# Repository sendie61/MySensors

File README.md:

# MySensors #
MySensors project. Wireless domotics sensors.<br>
Based on the open source project MySensors (http://www.mysensors.org)

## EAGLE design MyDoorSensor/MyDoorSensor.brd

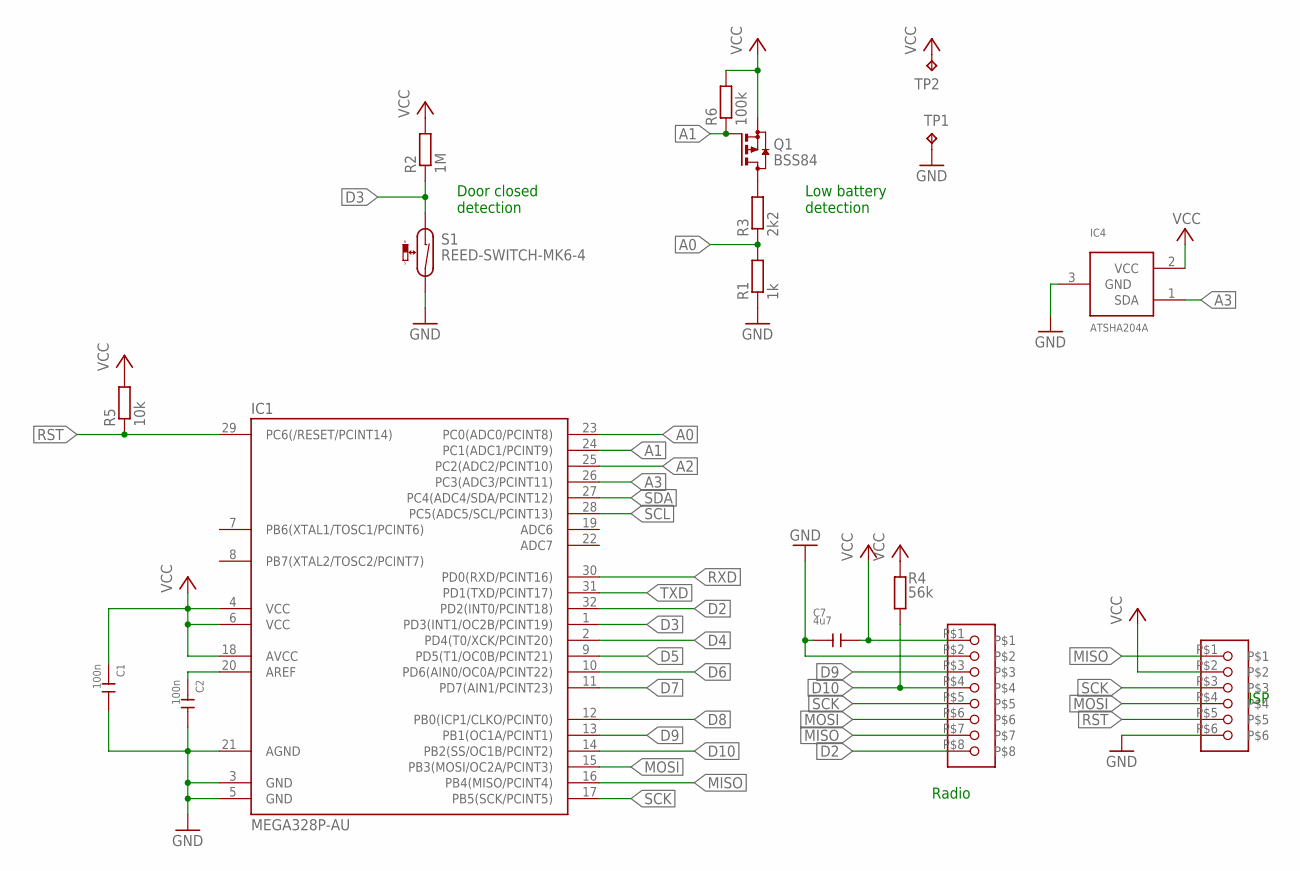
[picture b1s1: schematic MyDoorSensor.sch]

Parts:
C1, C2: 100n; C0603
C7: 4u7; C0805
IC1: MEGA328P-AU; TQFP32-08
IC4: ATSHA204A; SOT23
Q1: BSS84; SOT23
R1: 1k; R0805
R2: 1M; R0805
R3: 2k2; R0805
R4: 56k; R0805
R5: 10k; R0805
R6: 100k; R0805
S1: REED-SWITCH-MK6-4; MK6-4
TP1, TP2: TPPAD1-13; P1-13
U$1: NRF24; PINHD-1X08/NRF24
U$2: ISP

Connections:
A0: IC1.23 (PC0(ADC0/PCINT8)), R1.2, R3.1
A1: IC1.24 (PC1(ADC1/PCINT9)), Q1.1 (G), R6.1
A2: IC1.25 (PC2(ADC2/PCINT10))
A3: IC1.26 (PC3(ADC3/PCINT11)), IC4.1 (SDA)
D2: IC1.32 (PD2(INT0/PCINT18)), U$1.P$8
D3: IC1.1 (PD3(INT1/OC2B/PCINT19)), R2.1, S1.1
D4: IC1.2 (PD4(T0/XCK/PCINT20))
D5: IC1.9 (PD5(T1/OC0B/PCINT21))
D6: IC1.10 (PD6(AIN0/OC0A/PCINT22))
D7: IC1.11 (PD7(AIN1/PCINT23))
D8: IC1.12 (PB0(ICP1/CLKO/PCINT0))
D9: IC1.13 (PB1(OC1A/PCINT1)), U$1.P$3
D10: IC1.14 (PB2(SS/OC1B/PCINT2)), R4.1, U$1.P$4
GND: C1.2, C2.2, C7.1, IC1.3 (GND), IC1.5 (GND), IC1.21 (AGND), IC4.3 (GND), R1.1, S1.2, TP1.TP, U$1.P$2, U$2.P$6
MISO: IC1.16 (PB4(MISO/PCINT4)), U$1.P$7, U$2.P$1
MOSI: IC1.15 (PB3(MOSI/OC2A/PCINT3)), U$1.P$6, U$2.P$4
unnamed: Q1.3 (D), R3.2
unnamed: C2.1, IC1.20 (AREF)
RST: IC1.29 (PC6(/RESET/PCINT14)), R5.1, U$2.P$5
RXD: IC1.30 (PD0(RXD/PCINT16))
SCK: IC1.17 (PB5(SCK/PCINT5)), U$1.P$5, U$2.P$3
SCL: IC1.28 (PC5(ADC5/SCL/PCINT13))
SDA: IC1.27 (PC4(ADC4/SDA/PCINT12))
TXD: IC1.31 (PD1(TXD/PCINT17))
VCC: C1.1, C7.2, IC1.4 (VCC), IC1.6 (VCC), IC1.18 (AVCC), IC4.2 (VCC), Q1.2 (S), R2.2, R4.2, R5.2, R6.2, TP2.TP, U$1.P$1, U$2.P$2

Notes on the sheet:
Low battery detection
Door closed detection
ISP
Radio

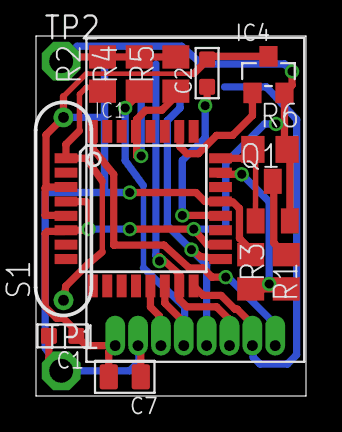
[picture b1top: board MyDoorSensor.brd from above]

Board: 2 copper layers, 15.0 x 20.0 mm, 17 parts (1 on the bottom side), 15 nets.

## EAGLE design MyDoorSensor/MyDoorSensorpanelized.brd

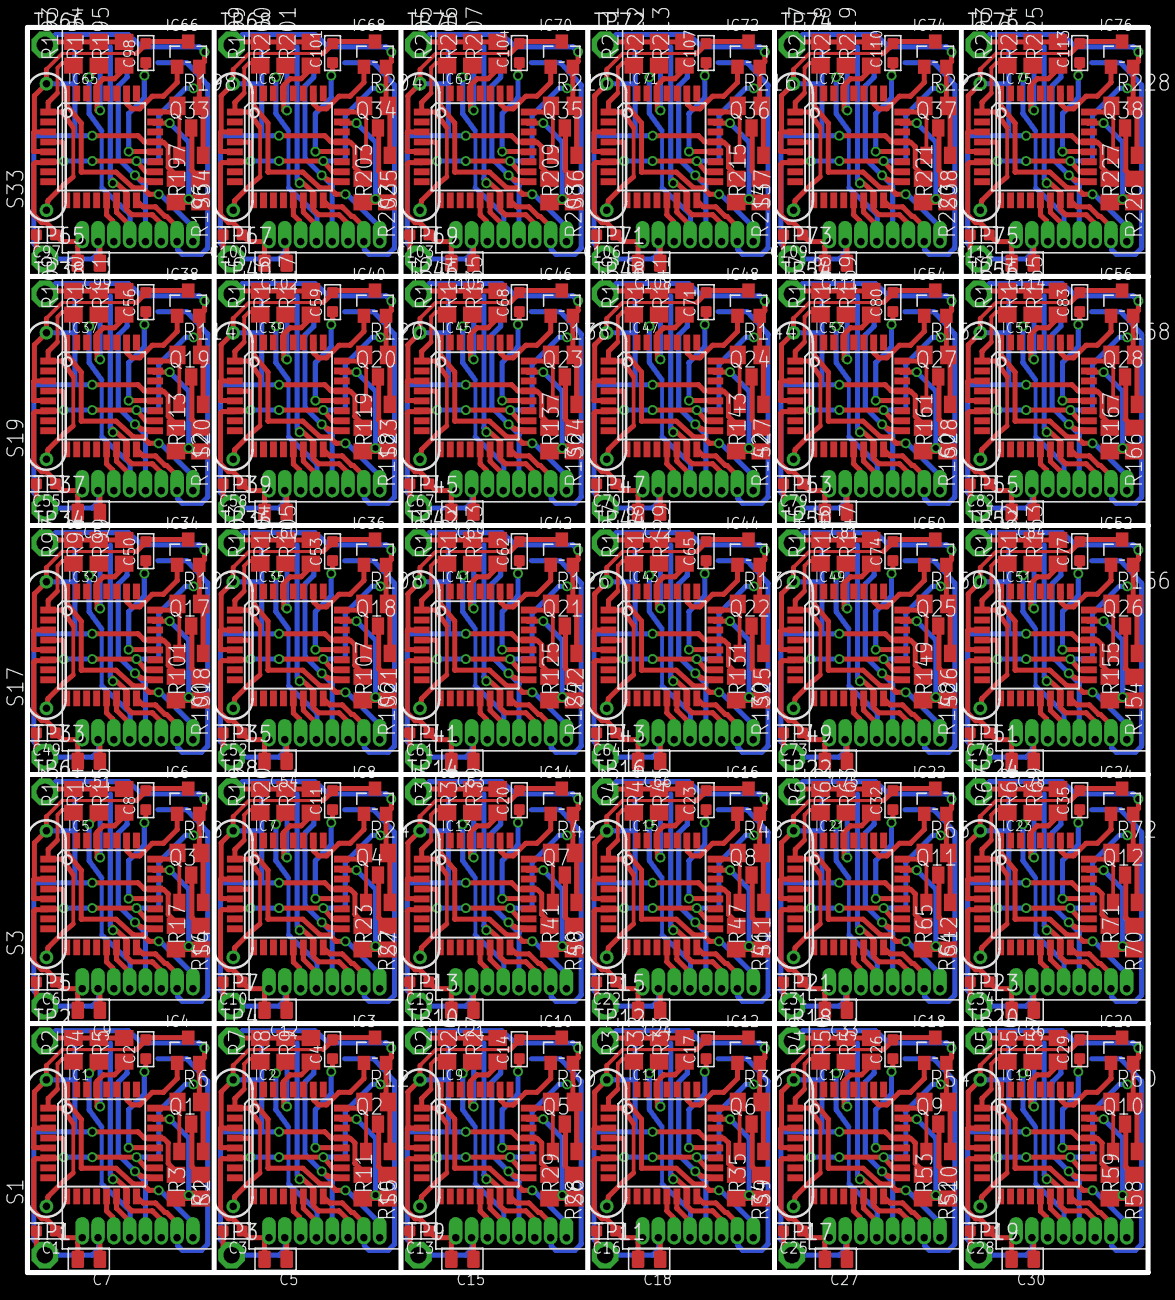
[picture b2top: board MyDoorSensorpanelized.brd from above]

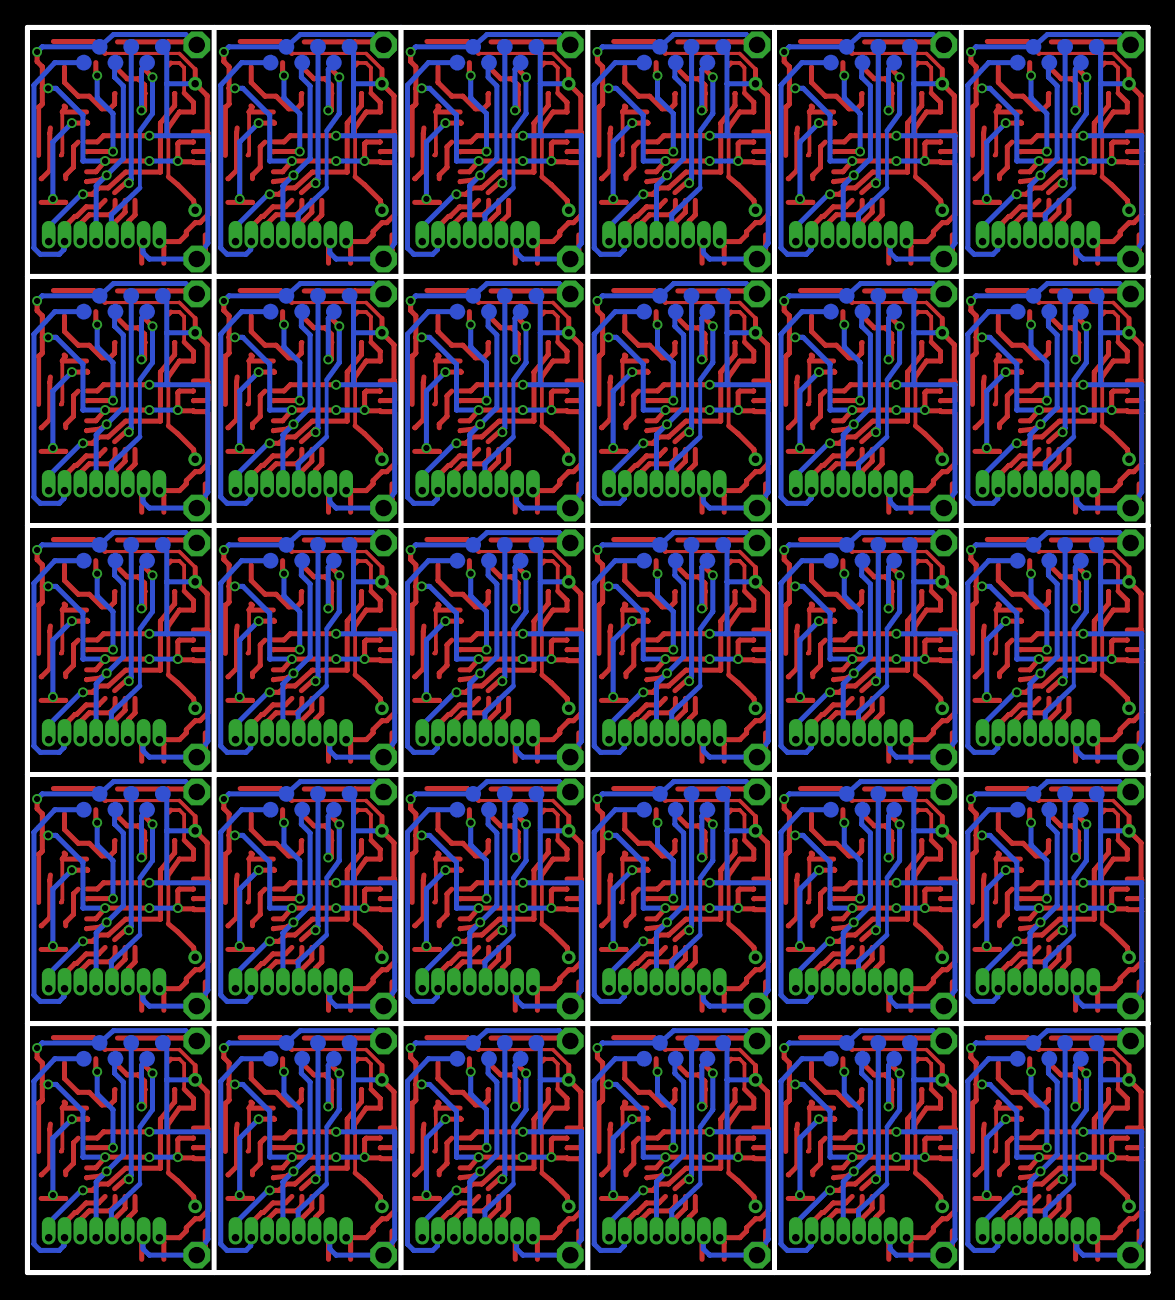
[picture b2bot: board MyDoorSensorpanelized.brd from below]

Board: 2 copper layers, 90.0 x 100.0 mm, 510 parts (30 on the bottom side), 450 nets.

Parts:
C1, C2, C3, C4, C6, C8, C10, C11, C13, C14, C16, C17, C19, C20, C22, C23, C25, C26, C28, C29, C31, C32, C34, C35, C49, C50, C52, C53, C55, C56, C58, C59, C61, C62, C64, C65, C67, C68, C70, C71, C73, C74, C76, C77, C79, C80, C82, C83, C97, C98, C100, C101, C103, C104, C106, C107, C109, C110, C112, C113: 100n; C0603
C5, C7, C9, C12, C15, C18, C21, C24, C27, C30, C33, C36, C51, C54, C57, C60, C63, C66, C69, C72, C75, C78, C81, C84, C99, C102, C105, C108, C111, C114: 4u7; C0805
IC1, IC2, IC5, IC7, IC9, IC11, IC13, IC15, IC17, IC19, IC21, IC23, IC33, IC35, IC37, IC39, IC41, IC43, IC45, IC47, IC49, IC51, IC53, IC55, IC65, IC67, IC69, IC71, IC73, IC75: MEGA328P-AU; TQFP32-08
IC3, IC4, IC6, IC8, IC10, IC12, IC14, IC16, IC18, IC20, IC22, IC24, IC34, IC36, IC38, IC40, IC42, IC44, IC46, IC48, IC50, IC52, IC54, IC56, IC66, IC68, IC70, IC72, IC74, IC76: ATSHA204A; SOT23
Q1, Q2, Q3, Q4, Q5, Q6, Q7, Q8, Q9, Q10, Q11, Q12, Q17, Q18, Q19, Q20, Q21, Q22, Q23, Q24, Q25, Q26, Q27, Q28, Q33, Q34, Q35, Q36, Q37, Q38: BSS84; SOT23
R1, R10, R16, R22, R28, R34, R40, R46, R52, R58, R64, R70, R100, R106, R112, R118, R124, R130, R136, R142, R148, R154, R160, R166, R196, R202, R208, R214, R220, R226: 1k; R0805
R2, R7, R13, R19, R25, R31, R37, R43, R49, R55, R61, R67, R97, R103, R109, R115, R121, R127, R133, R139, R145, R151, R157, R163, R193, R199, R205, R211, R217, R223: 1M; R0805
R3, R11, R17, R23, R29, R35, R41, R47, R53, R59, R65, R71, R101, R107, R113, R119, R125, R131, R137, R143, R149, R155, R161, R167, R197, R203, R209, R215, R221, R227: 2k2; R0805
R4, R8, R14, R20, R26, R32, R38, R44, R50, R56, R62, R68, R98, R104, R110, R116, R122, R128, R134, R140, R146, R152, R158, R164, R194, R200, R206, R212, R218, R224: 56k; R0805
R5, R9, R15, R21, R27, R33, R39, R45, R51, R57, R63, R69, R99, R105, R111, R117, R123, R129, R135, R141, R147, R153, R159, R165, R195, R201, R207, R213, R219, R225: 10k; R0805
R6, R12, R18, R24, R30, R36, R42, R48, R54, R60, R66, R72, R102, R108, R114, R120, R126, R132, R138, R144, R150, R156, R162, R168, R198, R204, R210, R216, R222, R228: 100k; R0805
S1, S2, S3, S4, S5, S6, S7, S8, S9, S10, S11, S12, S17, S18, S19, S20, S21, S22, S23, S24, S25, S26, S27, S28, S33, S34, S35, S36, S37, S38: REED-SWITCH-MK6-4; MK6-4
TP1, TP2, TP3, TP4, TP5, TP6, TP7, TP8, TP9, TP10, TP11, TP12, TP13, TP14, TP15, TP16, TP17, TP18, TP19, TP20, TP21, TP22, TP23, TP24, TP33, TP34, TP35, TP36, TP37, TP38, TP39, TP40, TP41, TP42, TP43, TP44, TP45, TP46, TP47, TP48, TP49, TP50, TP51, TP52, TP53, TP54, TP55, TP56, TP65, TP66, TP67, TP68, TP69, TP70, TP71, TP72, TP73, TP74, TP75, TP76: TPPAD1-13; P1-13
U$1, U$3, U$5, U$7, U$9, U$11, U$13, U$15, U$17, U$19, U$21, U$23, U$33, U$35, U$37, U$39, U$41, U$43, U$45, U$47, U$49, U$51, U$53, U$55, U$65, U$67, U$69, U$71, U$73, U$75: NRF24; PINHD-1X08/NRF24
U$2, U$4, U$6, U$8, U$10, U$12, U$14, U$16, U$18, U$20, U$22, U$24, U$34, U$36, U$38, U$40, U$42, U$44, U$46, U$48, U$50, U$52, U$54, U$56, U$66, U$68, U$70, U$72, U$74, U$76: ISP

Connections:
A0: IC1.23, R1.2, R3.1
A1: IC1.24, Q1.1, R6.1
A3: IC1.26, IC4.1
A4: IC2.23, R10.2, R11.1
A5: IC2.24, Q2.1, R12.1
A7: IC2.26, IC3.1
A8: IC5.23, R16.2, R17.1
A9: IC5.24, Q3.1, R18.1
A11: IC5.26, IC6.1
A12: IC7.23, R22.2, R23.1
A13: IC7.24, Q4.1, R24.1
A15: IC7.26, IC8.1
A16: IC9.23, R28.2, R29.1
A17: IC9.24, Q5.1, R30.1
A19: IC9.26, IC10.1
A20: IC11.23, R34.2, R35.1
A21: IC11.24, Q6.1, R36.1
A23: IC11.26, IC12.1
A24: IC13.23, R40.2, R41.1
A25: IC13.24, Q7.1, R42.1
A27: IC13.26, IC14.1
A28: IC15.23, R46.2, R47.1
A29: IC15.24, Q8.1, R48.1
A31: IC15.26, IC16.1
A32: IC17.23, R52.2, R53.1
A33: IC17.24, Q9.1, R54.1
A35: IC17.26, IC18.1
A36: IC19.23, R58.2, R59.1
A37: IC19.24, Q10.1, R60.1
A39: IC19.26, IC20.1
A40: IC21.23, R64.2, R65.1
A41: IC21.24, Q11.1, R66.1
A43: IC21.26, IC22.1
A44: IC23.23, R70.2, R71.1
A45: IC23.24, Q12.1, R72.1
A47: IC23.26, IC24.1
A64: IC33.23, R100.2, R101.1
A65: IC33.24, Q17.1, R102.1
A67: IC33.26, IC34.1
A68: IC35.23, R106.2, R107.1
A69: IC35.24, Q18.1, R108.1
A71: IC35.26, IC36.1
A72: IC37.23, R112.2, R113.1
A73: IC37.24, Q19.1, R114.1
A75: IC37.26, IC38.1
A76: IC39.23, R118.2, R119.1
A77: IC39.24, Q20.1, R120.1
A79: IC39.26, IC40.1
A80: IC41.23, R124.2, R125.1
A81: IC41.24, Q21.1, R126.1
A83: IC41.26, IC42.1
A84: IC43.23, R130.2, R131.1
A85: IC43.24, Q22.1, R132.1
A87: IC43.26, IC44.1
A88: IC45.23, R136.2, R137.1
A89: IC45.24, Q23.1, R138.1
A91: IC45.26, IC46.1
A92: IC47.23, R142.2, R143.1
A93: IC47.24, Q24.1, R144.1
A95: IC47.26, IC48.1
A96: IC49.23, R148.2, R149.1
A97: IC49.24, Q25.1, R150.1
A99: IC49.26, IC50.1
A100: IC51.23, R154.2, R155.1
A101: IC51.24, Q26.1, R156.1
A103: IC51.26, IC52.1
A104: IC53.23, R160.2, R161.1
A105: IC53.24, Q27.1, R162.1
A107: IC53.26, IC54.1
A108: IC55.23, R166.2, R167.1
A109: IC55.24, Q28.1, R168.1
A111: IC55.26, IC56.1
A128: IC65.23, R196.2, R197.1
A129: IC65.24, Q33.1, R198.1
A131: IC65.26, IC66.1
A132: IC67.23, R202.2, R203.1
A133: IC67.24, Q34.1, R204.1
A135: IC67.26, IC68.1
A136: IC69.23, R208.2, R209.1
A137: IC69.24, Q35.1, R210.1
A139: IC69.26, IC70.1
A140: IC71.23, R214.2, R215.1
A141: IC71.24, Q36.1, R216.1
A143: IC71.26, IC72.1
A144: IC73.23, R220.2, R221.1
A145: IC73.24, Q37.1, R222.1
A147: IC73.26, IC74.1
A148: IC75.23, R226.2, R227.1
A149: IC75.24, Q38.1, R228.1
A151: IC75.26, IC76.1
D2: IC1.32, U$1.P$8
D3: IC1.1, R2.1, S1.1
D9: IC1.13, U$1.P$3
D10: IC1.14, R4.1, U$1.P$4
D11: IC2.14, R8.1, U$3.P$4
D12: IC2.13, U$3.P$3
D15: IC2.32, U$3.P$8
D16: IC2.1, R7.1, S2.1
D20: IC5.14, R14.1, U$5.P$4
D21: IC5.13, U$5.P$3
D24: IC5.32, U$5.P$8
D25: IC5.1, R13.1, S3.1
D29: IC7.14, R20.1, U$7.P$4
D30: IC7.13, U$7.P$3
D33: IC7.32, U$7.P$8
D34: IC7.1, R19.1, S4.1
D38: IC9.14, R26.1, U$9.P$4
D39: IC9.13, U$9.P$3
D42: IC9.32, U$9.P$8
D43: IC9.1, R25.1, S5.1
D47: IC11.14, R32.1, U$11.P$4
D48: IC11.13, U$11.P$3
D51: IC11.32, U$11.P$8
D52: IC11.1, R31.1, S6.1
D56: IC13.14, R38.1, U$13.P$4
D57: IC13.13, U$13.P$3
D60: IC13.32, U$13.P$8
D61: IC13.1, R37.1, S7.1
D65: IC15.14, R44.1, U$15.P$4
D66: IC15.13, U$15.P$3
D69: IC15.32, U$15.P$8
D70: IC15.1, R43.1, S8.1
D74: IC17.14, R50.1, U$17.P$4
D75: IC17.13, U$17.P$3
D78: IC17.32, U$17.P$8
D79: IC17.1, R49.1, S9.1
D83: IC19.14, R56.1, U$19.P$4
D84: IC19.13, U$19.P$3
D87: IC19.32, U$19.P$8
D88: IC19.1, R55.1, S10.1
D92: IC21.14, R62.1, U$21.P$4
D93: IC21.13, U$21.P$3
D96: IC21.32, U$21.P$8
D97: IC21.1, R61.1, S11.1
D101: IC23.14, R68.1, U$23.P$4
D102: IC23.13, U$23.P$3
D105: IC23.32, U$23.P$8
D106: IC23.1, R67.1, S12.1
D146: IC33.14, R98.1, U$33.P$4
D147: IC33.13, U$33.P$3
D150: IC33.32, U$33.P$8
D151: IC33.1, R97.1, S17.1
D155: IC35.14, R104.1, U$35.P$4
D156: IC35.13, U$35.P$3
D159: IC35.32, U$35.P$8
D160: IC35.1, R103.1, S18.1
D164: IC37.14, R110.1, U$37.P$4
D165: IC37.13, U$37.P$3
D168: IC37.32, U$37.P$8
D169: IC37.1, R109.1, S19.1
D173: IC39.14, R116.1, U$39.P$4
D174: IC39.13, U$39.P$3
D177: IC39.32, U$39.P$8
D178: IC39.1, R115.1, S20.1
D182: IC41.14, R122.1, U$41.P$4
D183: IC41.13, U$41.P$3
D186: IC41.32, U$41.P$8
D187: IC41.1, R121.1, S21.1
D191: IC43.14, R128.1, U$43.P$4
D192: IC43.13, U$43.P$3
D195: IC43.32, U$43.P$8
D196: IC43.1, R127.1, S22.1
D200: IC45.14, R134.1, U$45.P$4
D201: IC45.13, U$45.P$3
D204: IC45.32, U$45.P$8
D205: IC45.1, R133.1, S23.1
D209: IC47.14, R140.1, U$47.P$4
D210: IC47.13, U$47.P$3
D213: IC47.32, U$47.P$8
D214: IC47.1, R139.1, S24.1
D218: IC49.14, R146.1, U$49.P$4
D219: IC49.13, U$49.P$3
D222: IC49.32, U$49.P$8
D223: IC49.1, R145.1, S25.1
D227: IC51.14, R152.1, U$51.P$4
D228: IC51.13, U$51.P$3
D231: IC51.32, U$51.P$8
D232: IC51.1, R151.1, S26.1
D236: IC53.14, R158.1, U$53.P$4
D237: IC53.13, U$53.P$3
D240: IC53.32, U$53.P$8
D241: IC53.1, R157.1, S27.1
D245: IC55.14, R164.1, U$55.P$4
D246: IC55.13, U$55.P$3
D249: IC55.32, U$55.P$8
D250: IC55.1, R163.1, S28.1
D290: IC65.14, R194.1, U$65.P$4
D291: IC65.13, U$65.P$3
D294: IC65.32, U$65.P$8
D295: IC65.1, R193.1, S33.1
D299: IC67.14, R200.1, U$67.P$4
D300: IC67.13, U$67.P$3
D303: IC67.32, U$67.P$8
D304: IC67.1, R199.1, S34.1
D308: IC69.14, R206.1, U$69.P$4
D309: IC69.13, U$69.P$3
D312: IC69.32, U$69.P$8
D313: IC69.1, R205.1, S35.1
D317: IC71.14, R212.1, U$71.P$4
D318: IC71.13, U$71.P$3
D321: IC71.32, U$71.P$8
D322: IC71.1, R211.1, S36.1
D326: IC73.14, R218.1, U$73.P$4
D327: IC73.13, U$73.P$3
D330: IC73.32, U$73.P$8
D331: IC73.1, R217.1, S37.1
D335: IC75.14, R224.1, U$75.P$4
D336: IC75.13, U$75.P$3
D339: IC75.32, U$75.P$8
D340: IC75.1, R223.1, S38.1
GND: C1.2, C2.2, C7.1, IC1.3, IC1.5, IC1.21, IC4.3, R1.1, S1.2, TP1.TP, U$1.P$2, U$2.P$6
GND1: C3.2, C4.2, C5.1, IC2.3, IC2.5, IC2.21, IC3.3, R10.1, S2.2, TP3.TP, U$3.P$2, U$4.P$6
GND2: C6.2, C8.2, C9.1, IC5.3, IC5.5, IC5.21, IC6.3, R16.1, S3.2, TP5.TP, U$5.P$2, U$6.P$6
GND3: C10.2, C11.2, C12.1, IC7.3, IC7.5, IC7.21, IC8.3, R22.1, S4.2, TP7.TP, U$7.P$2, U$8.P$6
GND4: C13.2, C14.2, C15.1, IC9.3, IC9.5, IC9.21, IC10.3, R28.1, S5.2, TP9.TP, U$9.P$2, U$10.P$6
GND5: C16.2, C17.2, C18.1, IC11.3, IC11.5, IC11.21, IC12.3, R34.1, S6.2, TP11.TP, U$11.P$2, U$12.P$6
GND6: C19.2, C20.2, C21.1, IC13.3, IC13.5, IC13.21, IC14.3, R40.1, S7.2, TP13.TP, U$13.P$2, U$14.P$6
GND7: C22.2, C23.2, C24.1, IC15.3, IC15.5, IC15.21, IC16.3, R46.1, S8.2, TP15.TP, U$15.P$2, U$16.P$6
GND8: C25.2, C26.2, C27.1, IC17.3, IC17.5, IC17.21, IC18.3, R52.1, S9.2, TP17.TP, U$17.P$2, U$18.P$6
GND9: C28.2, C29.2, C30.1, IC19.3, IC19.5, IC19.21, IC20.3, R58.1, S10.2, TP19.TP, U$19.P$2, U$20.P$6
GND10: C31.2, C32.2, C33.1, IC21.3, IC21.5, IC21.21, IC22.3, R64.1, S11.2, TP21.TP, U$21.P$2, U$22.P$6
GND11: C34.2, C35.2, C36.1, IC23.3, IC23.5, IC23.21, IC24.3, R70.1, S12.2, TP23.TP, U$23.P$2, U$24.P$6
GND16: C49.2, C50.2, C51.1, IC33.3, IC33.5, IC33.21, IC34.3, R100.1, S17.2, TP33.TP, U$33.P$2, U$34.P$6
GND17: C52.2, C53.2, C54.1, IC35.3, IC35.5, IC35.21, IC36.3, R106.1, S18.2, TP35.TP, U$35.P$2, U$36.P$6
GND18: C55.2, C56.2, C57.1, IC37.3, IC37.5, IC37.21, IC38.3, R112.1, S19.2, TP37.TP, U$37.P$2, U$38.P$6
GND19: C58.2, C59.2, C60.1, IC39.3, IC39.5, IC39.21, IC40.3, R118.1, S20.2, TP39.TP, U$39.P$2, U$40.P$6
GND20: C61.2, C62.2, C63.1, IC41.3, IC41.5, IC41.21, IC42.3, R124.1, S21.2, TP41.TP, U$41.P$2, U$42.P$6
GND21: C64.2, C65.2, C66.1, IC43.3, IC43.5, IC43.21, IC44.3, R130.1, S22.2, TP43.TP, U$43.P$2, U$44.P$6
GND22: C67.2, C68.2, C69.1, IC45.3, IC45.5, IC45.21, IC46.3, R136.1, S23.2, TP45.TP, U$45.P$2, U$46.P$6
GND23: C70.2, C71.2, C72.1, IC47.3, IC47.5, IC47.21, IC48.3, R142.1, S24.2, TP47.TP, U$47.P$2, U$48.P$6
GND24: C73.2, C74.2, C75.1, IC49.3, IC49.5, IC49.21, IC50.3, R148.1, S25.2, TP49.TP, U$49.P$2, U$50.P$6
GND25: C76.2, C77.2, C78.1, IC51.3, IC51.5, IC51.21, IC52.3, R154.1, S26.2, TP51.TP, U$51.P$2, U$52.P$6
GND26: C79.2, C80.2, C81.1, IC53.3, IC53.5, IC53.21, IC54.3, R160.1, S27.2, TP53.TP, U$53.P$2, U$54.P$6
GND27: C82.2, C83.2, C84.1, IC55.3, IC55.5, IC55.21, IC56.3, R166.1, S28.2, TP55.TP, U$55.P$2, U$56.P$6
GND32: C97.2, C98.2, C99.1, IC65.3, IC65.5, IC65.21, IC66.3, R196.1, S33.2, TP65.TP, U$65.P$2, U$66.P$6
GND33: C100.2, C101.2, C102.1, IC67.3, IC67.5, IC67.21, IC68.3, R202.1, S34.2, TP67.TP, U$67.P$2, U$68.P$6
GND34: C103.2, C104.2, C105.1, IC69.3, IC69.5, IC69.21, IC70.3, R208.1, S35.2, TP69.TP, U$69.P$2, U$70.P$6
GND35: C106.2, C107.2, C108.1, IC71.3, IC71.5, IC71.21, IC72.3, R214.1, S36.2, TP71.TP, U$71.P$2, U$72.P$6
GND36: C109.2, C110.2, C111.1, IC73.3, IC73.5, IC73.21, IC74.3, R220.1, S37.2, TP73.TP, U$73.P$2, U$74.P$6
GND37: C112.2, C113.2, C114.1, IC75.3, IC75.5, IC75.21, IC76.3, R226.1, S38.2, TP75.TP, U$75.P$2, U$76.P$6
MISO: IC1.16, U$1.P$7, U$2.P$1
MISO1: IC2.16, U$3.P$7, U$4.P$1
MISO2: IC5.16, U$5.P$7, U$6.P$1
MISO3: IC7.16, U$7.P$7, U$8.P$1
MISO4: IC9.16, U$9.P$7, U$10.P$1
MISO5: IC11.16, U$11.P$7, U$12.P$1
MISO6: IC13.16, U$13.P$7, U$14.P$1
MISO7: IC15.16, U$15.P$7, U$16.P$1
MISO8: IC17.16, U$17.P$7, U$18.P$1
MISO9: IC19.16, U$19.P$7, U$20.P$1
MISO10: IC21.16, U$21.P$7, U$22.P$1
MISO11: IC23.16, U$23.P$7, U$24.P$1
MISO16: IC33.16, U$33.P$7, U$34.P$1
MISO17: IC35.16, U$35.P$7, U$36.P$1
MISO18: IC37.16, U$37.P$7, U$38.P$1
MISO19: IC39.16, U$39.P$7, U$40.P$1
MISO20: IC41.16, U$41.P$7, U$42.P$1
MISO21: IC43.16, U$43.P$7, U$44.P$1
MISO22: IC45.16, U$45.P$7, U$46.P$1
MISO23: IC47.16, U$47.P$7, U$48.P$1
MISO24: IC49.16, U$49.P$7, U$50.P$1
MISO25: IC51.16, U$51.P$7, U$52.P$1
MISO26: IC53.16, U$53.P$7, U$54.P$1
MISO27: IC55.16, U$55.P$7, U$56.P$1
MISO32: IC65.16, U$65.P$7, U$66.P$1
MISO33: IC67.16, U$67.P$7, U$68.P$1
MISO34: IC69.16, U$69.P$7, U$70.P$1
MISO35: IC71.16, U$71.P$7, U$72.P$1
MISO36: IC73.16, U$73.P$7, U$74.P$1
MISO37: IC75.16, U$75.P$7, U$76.P$1
MOSI: IC1.15, U$1.P$6, U$2.P$4
MOSI1: IC2.15, U$3.P$6, U$4.P$4
MOSI2: IC5.15, U$5.P$6, U$6.P$4
MOSI3: IC7.15, U$7.P$6, U$8.P$4
MOSI4: IC9.15, U$9.P$6, U$10.P$4
MOSI5: IC11.15, U$11.P$6, U$12.P$4
MOSI6: IC13.15, U$13.P$6, U$14.P$4
MOSI7: IC15.15, U$15.P$6, U$16.P$4
MOSI8: IC17.15, U$17.P$6, U$18.P$4
MOSI9: IC19.15, U$19.P$6, U$20.P$4
MOSI10: IC21.15, U$21.P$6, U$22.P$4
MOSI11: IC23.15, U$23.P$6, U$24.P$4
MOSI16: IC33.15, U$33.P$6, U$34.P$4
MOSI17: IC35.15, U$35.P$6, U$36.P$4
MOSI18: IC37.15, U$37.P$6, U$38.P$4
MOSI19: IC39.15, U$39.P$6, U$40.P$4
MOSI20: IC41.15, U$41.P$6, U$42.P$4
MOSI21: IC43.15, U$43.P$6, U$44.P$4
MOSI22: IC45.15, U$45.P$6, U$46.P$4
MOSI23: IC47.15, U$47.P$6, U$48.P$4
MOSI24: IC49.15, U$49.P$6, U$50.P$4
MOSI25: IC51.15, U$51.P$6, U$52.P$4
MOSI26: IC53.15, U$53.P$6, U$54.P$4
MOSI27: IC55.15, U$55.P$6, U$56.P$4
MOSI32: IC65.15, U$65.P$6, U$66.P$4
MOSI33: IC67.15, U$67.P$6, U$68.P$4
MOSI34: IC69.15, U$69.P$6, U$70.P$4
MOSI35: IC71.15, U$71.P$6, U$72.P$4
MOSI36: IC73.15, U$73.P$6, U$74.P$4
MOSI37: IC75.15, U$75.P$6, U$76.P$4
unnamed: C4.1, IC2.20
unnamed: Q1.3, R3.2
unnamed: Q2.3, R11.2
unnamed: C2.1, IC1.20
unnamed: C8.1, IC5.20
unnamed: Q3.3, R17.2
unnamed: C11.1, IC7.20
unnamed: Q4.3, R23.2
unnamed: C14.1, IC9.20
unnamed: Q5.3, R29.2
unnamed: C17.1, IC11.20
unnamed: Q6.3, R35.2
unnamed: C20.1, IC13.20
unnamed: Q7.3, R41.2
unnamed: C23.1, IC15.20
unnamed: Q8.3, R47.2
unnamed: C26.1, IC17.20
unnamed: Q9.3, R53.2
unnamed: C29.1, IC19.20
unnamed: Q10.3, R59.2
unnamed: C32.1, IC21.20
unnamed: Q11.3, R65.2
unnamed: C35.1, IC23.20
unnamed: Q12.3, R71.2
unnamed: C50.1, IC33.20
unnamed: Q17.3, R101.2
unnamed: C53.1, IC35.20
unnamed: Q18.3, R107.2
unnamed: C56.1, IC37.20
unnamed: Q19.3, R113.2
unnamed: C59.1, IC39.20
unnamed: Q20.3, R119.2
unnamed: C62.1, IC41.20
unnamed: Q21.3, R125.2
unnamed: C65.1, IC43.20
unnamed: Q22.3, R131.2
unnamed: C68.1, IC45.20
unnamed: Q23.3, R137.2
unnamed: C71.1, IC47.20
unnamed: Q24.3, R143.2
unnamed: C74.1, IC49.20
unnamed: Q25.3, R149.2
unnamed: C77.1, IC51.20
unnamed: Q26.3, R155.2
unnamed: C80.1, IC53.20
unnamed: Q27.3, R161.2
unnamed: C83.1, IC55.20
unnamed: Q28.3, R167.2
unnamed: C98.1, IC65.20
unnamed: Q33.3, R197.2
unnamed: C101.1, IC67.20
unnamed: Q34.3, R203.2
unnamed: C104.1, IC69.20
unnamed: Q35.3, R209.2
unnamed: C107.1, IC71.20
unnamed: Q36.3, R215.2
unnamed: C110.1, IC73.20
unnamed: Q37.3, R221.2
unnamed: C113.1, IC75.20
unnamed: Q38.3, R227.2
RST: IC1.29, R5.1, U$2.P$5
RST1: IC2.29, R9.1, U$4.P$5
RST2: IC5.29, R15.1, U$6.P$5
RST3: IC7.29, R21.1, U$8.P$5
RST4: IC9.29, R27.1, U$10.P$5
RST5: IC11.29, R33.1, U$12.P$5
RST6: IC13.29, R39.1, U$14.P$5
RST7: IC15.29, R45.1, U$16.P$5
RST8: IC17.29, R51.1, U$18.P$5
RST9: IC19.29, R57.1, U$20.P$5
RST10: IC21.29, R63.1, U$22.P$5
RST11: IC23.29, R69.1, U$24.P$5
RST16: IC33.29, R99.1, U$34.P$5
RST17: IC35.29, R105.1, U$36.P$5
RST18: IC37.29, R111.1, U$38.P$5
RST19: IC39.29, R117.1, U$40.P$5
RST20: IC41.29, R123.1, U$42.P$5
RST21: IC43.29, R129.1, U$44.P$5
RST22: IC45.29, R135.1, U$46.P$5
RST23: IC47.29, R141.1, U$48.P$5
RST24: IC49.29, R147.1, U$50.P$5
RST25: IC51.29, R153.1, U$52.P$5
RST26: IC53.29, R159.1, U$54.P$5
RST27: IC55.29, R165.1, U$56.P$5
RST32: IC65.29, R195.1, U$66.P$5
RST33: IC67.29, R201.1, U$68.P$5
RST34: IC69.29, R207.1, U$70.P$5
RST35: IC71.29, R213.1, U$72.P$5
RST36: IC73.29, R219.1, U$74.P$5
RST37: IC75.29, R225.1, U$76.P$5
SCK: IC1.17, U$1.P$5, U$2.P$3
SCK1: IC2.17, U$3.P$5, U$4.P$3
SCK2: IC5.17, U$5.P$5, U$6.P$3
SCK3: IC7.17, U$7.P$5, U$8.P$3
SCK4: IC9.17, U$9.P$5, U$10.P$3
SCK5: IC11.17, U$11.P$5, U$12.P$3
SCK6: IC13.17, U$13.P$5, U$14.P$3
SCK7: IC15.17, U$15.P$5, U$16.P$3
SCK8: IC17.17, U$17.P$5, U$18.P$3
SCK9: IC19.17, U$19.P$5, U$20.P$3
SCK10: IC21.17, U$21.P$5, U$22.P$3
SCK11: IC23.17, U$23.P$5, U$24.P$3
SCK16: IC33.17, U$33.P$5, U$34.P$3
SCK17: IC35.17, U$35.P$5, U$36.P$3
SCK18: IC37.17, U$37.P$5, U$38.P$3
SCK19: IC39.17, U$39.P$5, U$40.P$3
SCK20: IC41.17, U$41.P$5, U$42.P$3
SCK21: IC43.17, U$43.P$5, U$44.P$3
SCK22: IC45.17, U$45.P$5, U$46.P$3
SCK23: IC47.17, U$47.P$5, U$48.P$3
SCK24: IC49.17, U$49.P$5, U$50.P$3
SCK25: IC51.17, U$51.P$5, U$52.P$3
SCK26: IC53.17, U$53.P$5, U$54.P$3
SCK27: IC55.17, U$55.P$5, U$56.P$3
SCK32: IC65.17, U$65.P$5, U$66.P$3
SCK33: IC67.17, U$67.P$5, U$68.P$3
SCK34: IC69.17, U$69.P$5, U$70.P$3
SCK35: IC71.17, U$71.P$5, U$72.P$3
SCK36: IC73.17, U$73.P$5, U$74.P$3
SCK37: IC75.17, U$75.P$5, U$76.P$3
VCC: C1.1, C7.2, IC1.4, IC1.6, IC1.18, IC4.2, Q1.2, R2.2, R4.2, R5.2, R6.2, TP2.TP, U$1.P$1, U$2.P$2
VCC1: C3.1, C5.2, IC2.4, IC2.6, IC2.18, IC3.2, Q2.2, R7.2, R8.2, R9.2, R12.2, TP4.TP, U$3.P$1, U$4.P$2
VCC2: C6.1, C9.2, IC5.4, IC5.6, IC5.18, IC6.2, Q3.2, R13.2, R14.2, R15.2, R18.2, TP6.TP, U$5.P$1, U$6.P$2
VCC3: C10.1, C12.2, IC7.4, IC7.6, IC7.18, IC8.2, Q4.2, R19.2, R20.2, R21.2, R24.2, TP8.TP, U$7.P$1, U$8.P$2
VCC4: C13.1, C15.2, IC9.4, IC9.6, IC9.18, IC10.2, Q5.2, R25.2, R26.2, R27.2, R30.2, TP10.TP, U$9.P$1, U$10.P$2
VCC5: C16.1, C18.2, IC11.4, IC11.6, IC11.18, IC12.2, Q6.2, R31.2, R32.2, R33.2, R36.2, TP12.TP, U$11.P$1, U$12.P$2
VCC6: C19.1, C21.2, IC13.4, IC13.6, IC13.18, IC14.2, Q7.2, R37.2, R38.2, R39.2, R42.2, TP14.TP, U$13.P$1, U$14.P$2
VCC7: C22.1, C24.2, IC15.4, IC15.6, IC15.18, IC16.2, Q8.2, R43.2, R44.2, R45.2, R48.2, TP16.TP, U$15.P$1, U$16.P$2
VCC8: C25.1, C27.2, IC17.4, IC17.6, IC17.18, IC18.2, Q9.2, R49.2, R50.2, R51.2, R54.2, TP18.TP, U$17.P$1, U$18.P$2
VCC9: C28.1, C30.2, IC19.4, IC19.6, IC19.18, IC20.2, Q10.2, R55.2, R56.2, R57.2, R60.2, TP20.TP, U$19.P$1, U$20.P$2
VCC10: C31.1, C33.2, IC21.4, IC21.6, IC21.18, IC22.2, Q11.2, R61.2, R62.2, R63.2, R66.2, TP22.TP, U$21.P$1, U$22.P$2
VCC11: C34.1, C36.2, IC23.4, IC23.6, IC23.18, IC24.2, Q12.2, R67.2, R68.2, R69.2, R72.2, TP24.TP, U$23.P$1, U$24.P$2
VCC16: C49.1, C51.2, IC33.4, IC33.6, IC33.18, IC34.2, Q17.2, R97.2, R98.2, R99.2, R102.2, TP34.TP, U$33.P$1, U$34.P$2
VCC17: C52.1, C54.2, IC35.4, IC35.6, IC35.18, IC36.2, Q18.2, R103.2, R104.2, R105.2, R108.2, TP36.TP, U$35.P$1, U$36.P$2
VCC18: C55.1, C57.2, IC37.4, IC37.6, IC37.18, IC38.2, Q19.2, R109.2, R110.2, R111.2, R114.2, TP38.TP, U$37.P$1, U$38.P$2
VCC19: C58.1, C60.2, IC39.4, IC39.6, IC39.18, IC40.2, Q20.2, R115.2, R116.2, R117.2, R120.2, TP40.TP, U$39.P$1, U$40.P$2
VCC20: C61.1, C63.2, IC41.4, IC41.6, IC41.18, IC42.2, Q21.2, R121.2, R122.2, R123.2, R126.2, TP42.TP, U$41.P$1, U$42.P$2
VCC21: C64.1, C66.2, IC43.4, IC43.6, IC43.18, IC44.2, Q22.2, R127.2, R128.2, R129.2, R132.2, TP44.TP, U$43.P$1, U$44.P$2
VCC22: C67.1, C69.2, IC45.4, IC45.6, IC45.18, IC46.2, Q23.2, R133.2, R134.2, R135.2, R138.2, TP46.TP, U$45.P$1, U$46.P$2
VCC23: C70.1, C72.2, IC47.4, IC47.6, IC47.18, IC48.2, Q24.2, R139.2, R140.2, R141.2, R144.2, TP48.TP, U$47.P$1, U$48.P$2
VCC24: C73.1, C75.2, IC49.4, IC49.6, IC49.18, IC50.2, Q25.2, R145.2, R146.2, R147.2, R150.2, TP50.TP, U$49.P$1, U$50.P$2
VCC25: C76.1, C78.2, IC51.4, IC51.6, IC51.18, IC52.2, Q26.2, R151.2, R152.2, R153.2, R156.2, TP52.TP, U$51.P$1, U$52.P$2
VCC26: C79.1, C81.2, IC53.4, IC53.6, IC53.18, IC54.2, Q27.2, R157.2, R158.2, R159.2, R162.2, TP54.TP, U$53.P$1, U$54.P$2
VCC27: C82.1, C84.2, IC55.4, IC55.6, IC55.18, IC56.2, Q28.2, R163.2, R164.2, R165.2, R168.2, TP56.TP, U$55.P$1, U$56.P$2
VCC32: C97.1, C99.2, IC65.4, IC65.6, IC65.18, IC66.2, Q33.2, R193.2, R194.2, R195.2, R198.2, TP66.TP, U$65.P$1, U$66.P$2
VCC33: C100.1, C102.2, IC67.4, IC67.6, IC67.18, IC68.2, Q34.2, R199.2, R200.2, R201.2, R204.2, TP68.TP, U$67.P$1, U$68.P$2
VCC34: C103.1, C105.2, IC69.4, IC69.6, IC69.18, IC70.2, Q35.2, R205.2, R206.2, R207.2, R210.2, TP70.TP, U$69.P$1, U$70.P$2
VCC35: C106.1, C108.2, IC71.4, IC71.6, IC71.18, IC72.2, Q36.2, R211.2, R212.2, R213.2, R216.2, TP72.TP, U$71.P$1, U$72.P$2
VCC36: C109.1, C111.2, IC73.4, IC73.6, IC73.18, IC74.2, Q37.2, R217.2, R218.2, R219.2, R222.2, TP74.TP, U$73.P$1, U$74.P$2
VCC37: C112.1, C114.2, IC75.4, IC75.6, IC75.18, IC76.2, Q38.2, R223.2, R224.2, R225.2, R228.2, TP76.TP, U$75.P$1, U$76.P$2

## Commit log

2016-02-23 initial
2016-02-26 readme
2016-02-26 url fixed
2016-02-26 linebreak
2016-02-29 pdf's added
2016-03-02 Routed!!
2016-03-02 pdf's
2016-03-03 Panel added
2016-03-07 topsolid draft
